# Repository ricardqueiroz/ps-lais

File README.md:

# ps-lais
Contém todos os arquivos produzidos durante o processo seletivo do Laboratório de Inovação Tecnológica em Saúde

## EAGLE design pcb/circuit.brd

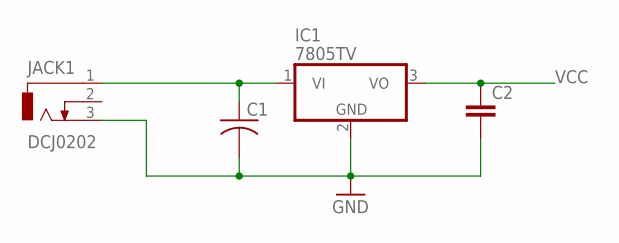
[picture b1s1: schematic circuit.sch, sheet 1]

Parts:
C1: C-US025-030X050; C025-030X050
C2: C-EU025-030X050; C025-030X050
IC1: 7805TV; TO220V
JACK1: DCJ0202

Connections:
GND: C1.2, C2.2, IC1.2 (GND), JACK1.3; also elsewhere on the board
VCC: C2.1, IC1.3 (VO); also elsewhere on the board
VIN: C1.1, IC1.1 (VI), JACK1.1

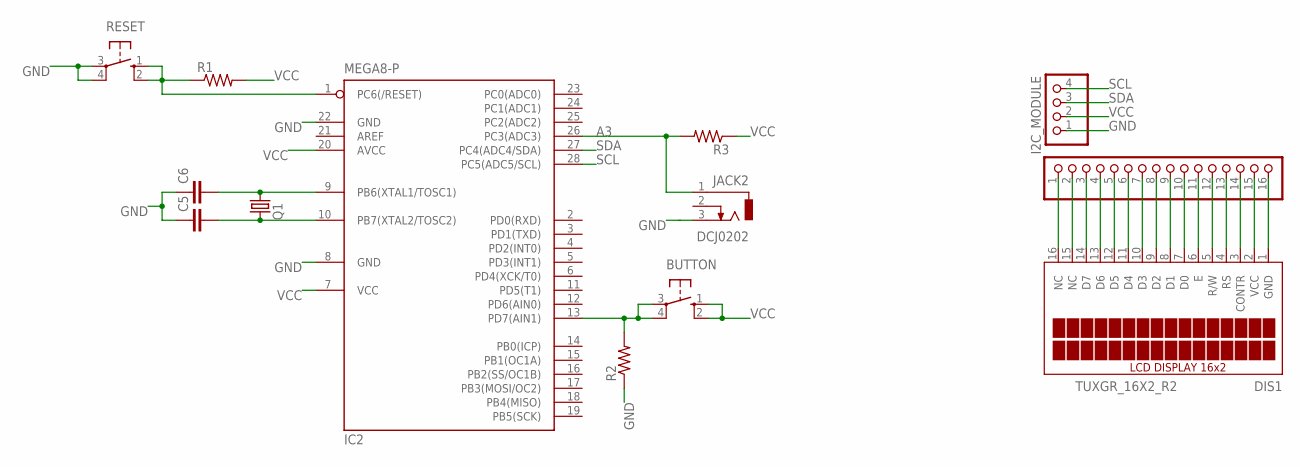
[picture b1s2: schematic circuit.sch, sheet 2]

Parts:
BUTTON: 10-XX; B3F-10XX
C5, C6: C-EU025-025X050; C025-025X050
DIS1: TUXGR_16X2_R2
I2C_MODULE: PINHD-1X4; 1X04
IC2: MEGA8-P; DIL28-3
JACK2: DCJ0202
JP1: PINHD-1X16; 1X16
Q1: CRYSTALHC49U-V; HC49U-V
R1, R2, R3: R-US_0207/10; 0207/10
RESET: 10-XX; B3F-10XX

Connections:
A3: IC2.26 (PC3(ADC3)), JACK2.1, R3.2
D7: BUTTON.3, BUTTON.4 (P1), IC2.13 (PD7(AIN1)), R2.2
GND: C5.1, C6.1, I2C_MODULE.1, IC2.8 (GND), IC2.22 (GND), JACK2.3, R2.1, RESET.3, RESET.4 (P1); also elsewhere on the board
unnamed: DIS1.1 (GND), JP1.16
unnamed: DIS1.2 (VCC), JP1.15
unnamed: DIS1.3 (CONTR), JP1.14
unnamed: C6.2, IC2.9 (PB6(XTAL1/TOSC1)), Q1.2
unnamed: DIS1.4 (RS), JP1.13
unnamed: C5.2, IC2.10 (PB7(XTAL2/TOSC2)), Q1.1
unnamed: DIS1.5 (R/W), JP1.12
unnamed: DIS1.6 (E), JP1.11
unnamed: DIS1.7 (D0), JP1.10
unnamed: DIS1.8 (D1), JP1.9
unnamed: DIS1.9 (D2), JP1.8
unnamed: DIS1.10 (D3), JP1.7
unnamed: DIS1.11 (D4), JP1.6
unnamed: DIS1.12 (D5), JP1.5
unnamed: DIS1.13 (D6), JP1.4
unnamed: DIS1.14 (D7), JP1.3
unnamed: DIS1.15 (NC), JP1.2
unnamed: DIS1.16 (NC), JP1.1
unnamed: IC2.1 (PC6(/RESET)), R1.1, RESET.1 (S), RESET.2 (S1)
SCL: I2C_MODULE.4, IC2.28 (PC5(ADC5/SCL))
SDA: I2C_MODULE.3, IC2.27 (PC4(ADC4/SDA))
VCC: BUTTON.1 (S), BUTTON.2 (S1), I2C_MODULE.2, IC2.7 (VCC), IC2.20 (AVCC), R1.2, R3.1; also elsewhere on the board

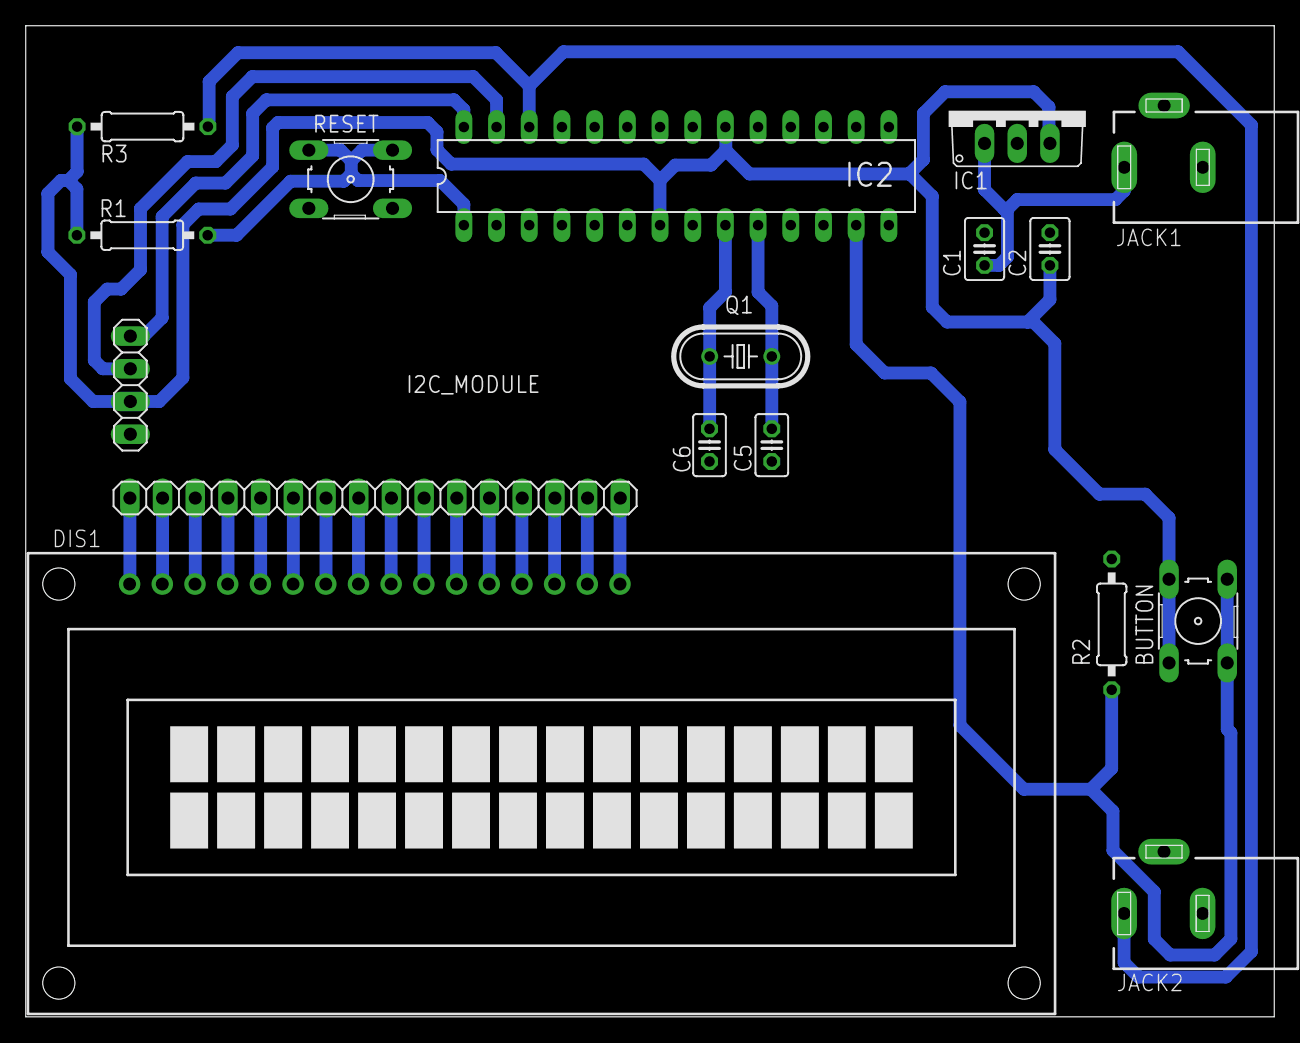
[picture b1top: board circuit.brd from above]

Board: 2 copper layers, 97.0 x 77.0 mm, 17 parts (0 on the bottom side), 26 nets.

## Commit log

2020-12-21 Arquivos produzidos para o PS
